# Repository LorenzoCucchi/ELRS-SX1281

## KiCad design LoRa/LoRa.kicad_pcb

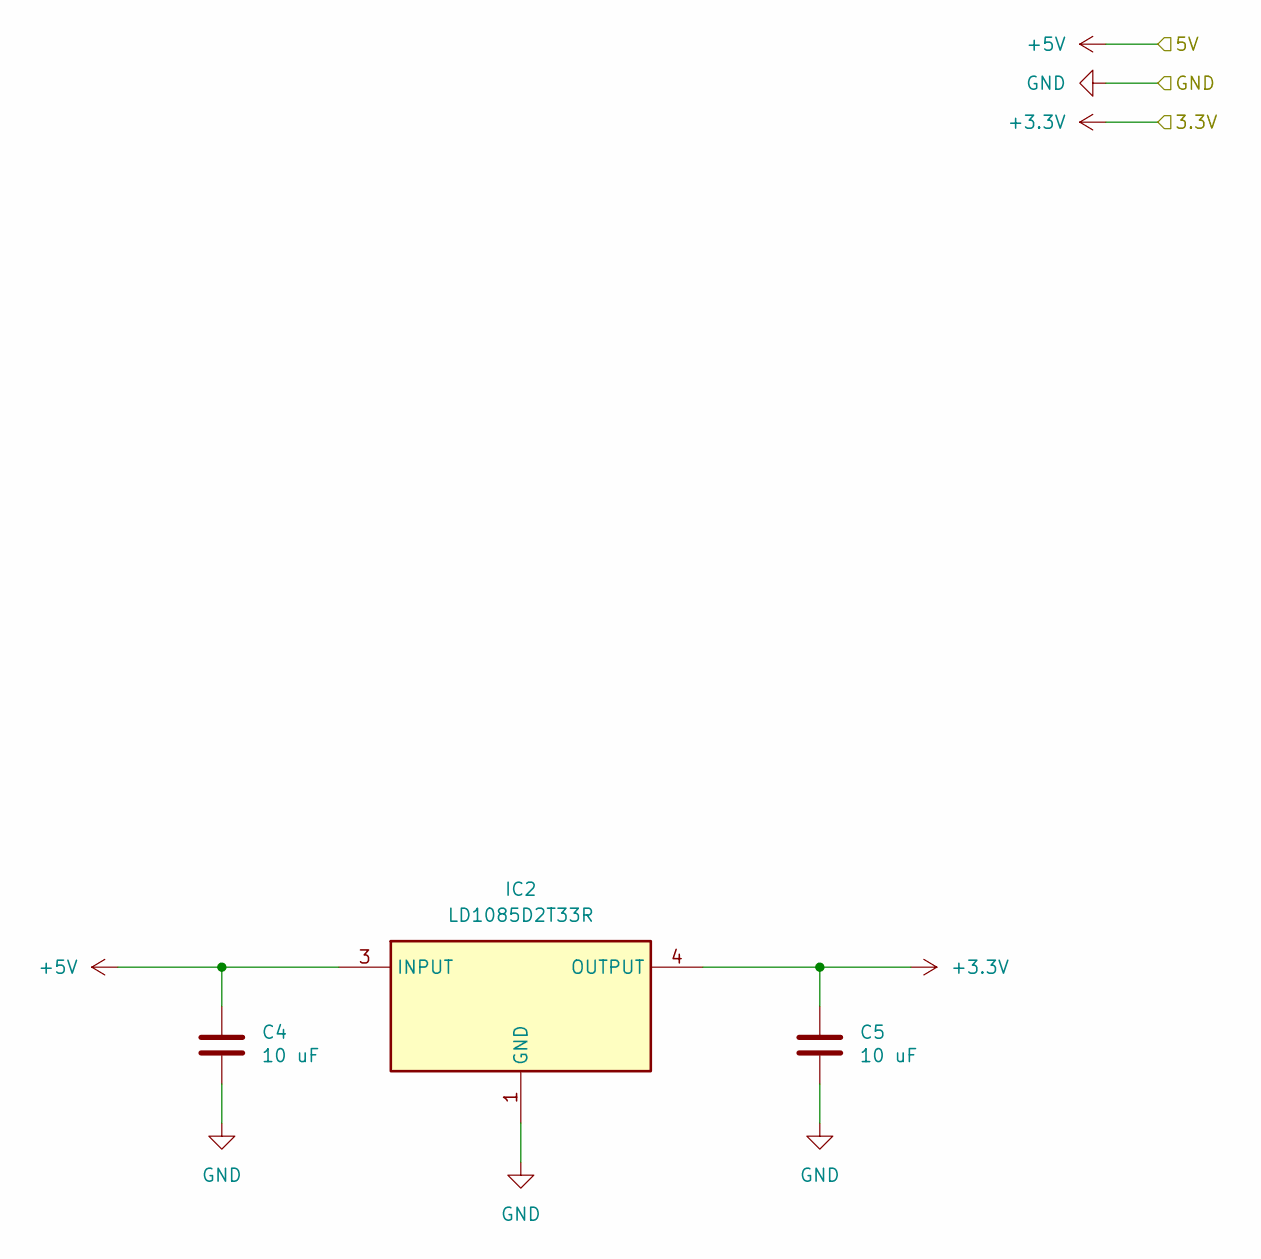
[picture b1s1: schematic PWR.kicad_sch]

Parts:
C4, C5: 10 uF; C_0603_1608Metric_Pad1.08x0.95mm_HandSolder
IC2: LD1085D2T33R; Mouser Part Number 511-LD1085D2T33-TR

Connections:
+3.3V: C5.1, IC2.4 (OUTPUT); also elsewhere on the board
+5V: C4.1, IC2.3 (INPUT); also elsewhere on the board
GND: C4.2, C5.2, IC2.1 (GND); also elsewhere on the board

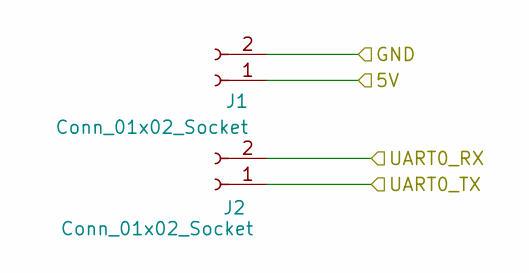
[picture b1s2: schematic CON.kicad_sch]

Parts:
J1, J2: Conn_01x02_Socket; PinHeader_1x02_P2.54mm_Vertical

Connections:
+5V: J1.1; also elsewhere on the board
GND: J1.2; also elsewhere on the board
UART0_RX: J2.2; also elsewhere on the board
UART0_TX: J2.1; also elsewhere on the board

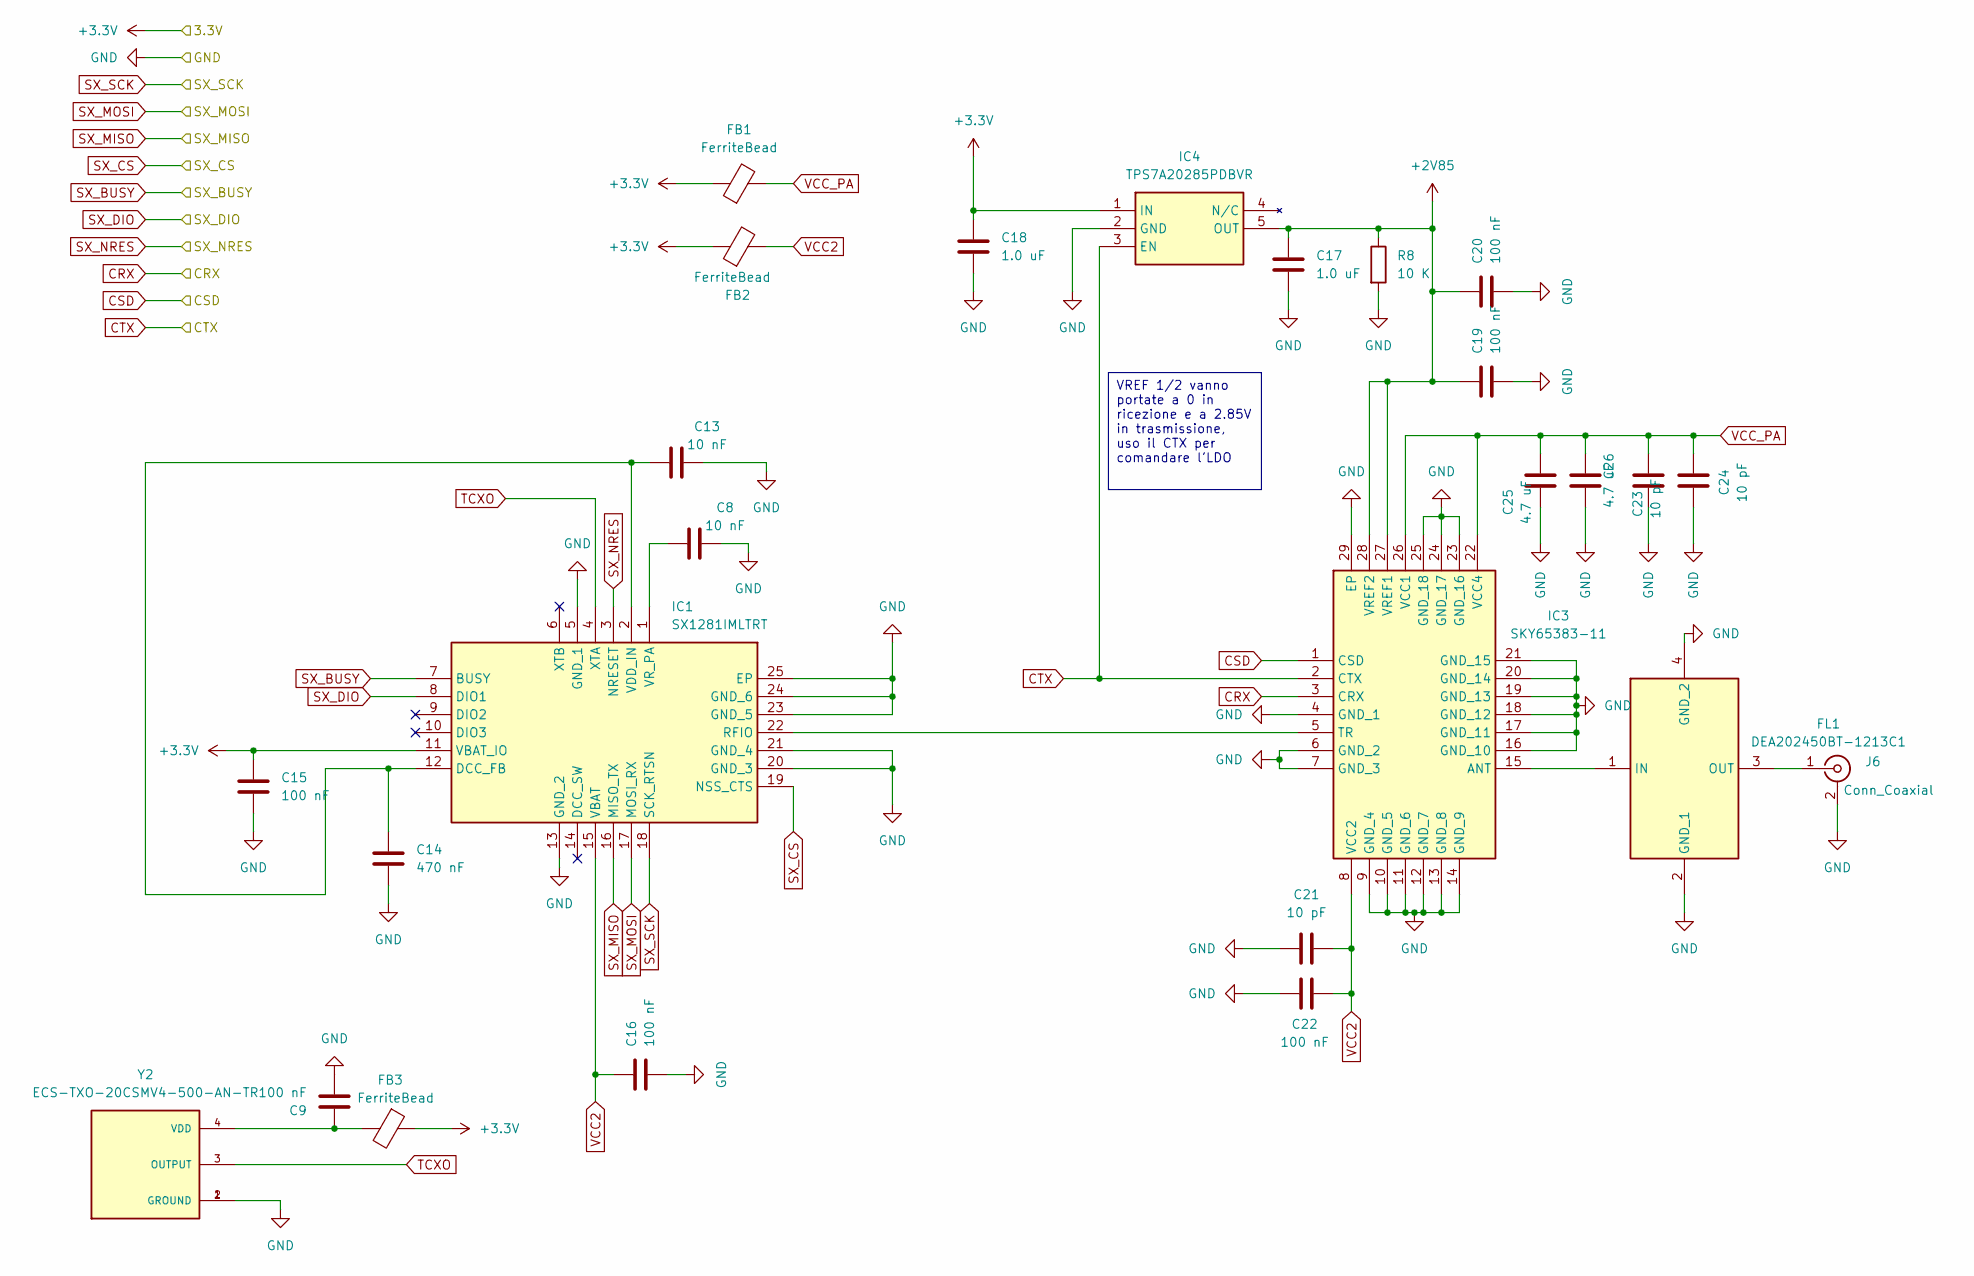
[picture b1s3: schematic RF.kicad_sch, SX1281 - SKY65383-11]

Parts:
C8, C13: 10 nF; C_0603_1608Metric_Pad1.08x0.95mm_HandSolder
C9, C15, C16, C19, C20, C22: 100 nF; C_0603_1608Metric_Pad1.08x0.95mm_HandSolder
C14: 470 nF; C_0603_1608Metric_Pad1.08x0.95mm_HandSolder
C17, C18: 1.0 uF; C_0603_1608Metric_Pad1.08x0.95mm_HandSolder
C21, C23, C24: 10 pF; C_0603_1608Metric_Pad1.08x0.95mm_HandSolder
C25, C26: 4.7 uF; C_0603_1608Metric_Pad1.08x0.95mm_HandSolder
FB1, FB2, FB3: FerriteBead; R_0603_1608Metric_Pad0.98x0.95mm_HandSolder
FL1: DEA202450BT-1213C1; DEA202450BT1213C1; Mouser Part Number 810-DEA22450BT1213C1
IC1: SX1281IMLTRT; QFN50P400X400X100-25N-D; Mouser Part Number 947-SX1281IMLTRT
IC3: SKY65383-11; SKY6538311; Mouser Part Number 873-SKY65383-11
IC4: TPS7A20285PDBVR; SOT95P280X145-5N; Mouser Part Number 595-TPS7A20285PDBVR
J6: Conn_Coaxial; SMA_Samtec_SMA-J-P-H-ST-EM1_EdgeMount
R8: 10 K; R_0603_1608Metric_Pad0.98x0.95mm_HandSolder
Y2: ECS-TXO-20CSMV4-500-AN-TR; OSC_ECS-TXO-20CSMV4-520-AN-TR; PARTREV N/A

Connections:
+2V85: C17.1, C19.1, C20.1, IC3.27 (VREF1), IC3.28 (VREF2), IC4.5 (OUT), R8.1
+3.3V: C15.1, C18.1, FB1.1, FB2.1, FB3.1, IC1.11 (VBAT_IO), IC4.1 (IN); also elsewhere on the board
CRX: IC3.3 (CRX); also elsewhere on the board
CSD: IC3.1 (CSD); also elsewhere on the board
CTX: IC3.2 (CTX), IC4.3 (EN); also elsewhere on the board
GND: C8.2, C9.2, C13.2, C14.2, C15.2, C16.2, C17.2, C18.2, C19.2, C20.2, C21.2, C22.2, C23.2, C24.2, C25.2, C26.2, FL1.2 (GND_1), FL1.4 (GND_2), IC1.5 (GND_1), IC1.13 (GND_2), IC1.20 (GND_3), IC1.21 (GND_4), IC1.23 (GND_5), IC1.24 (GND_6), IC1.25 (EP), IC3.4 (GND_1), IC3.6 (GND_2), IC3.7 (GND_3), IC3.9 (GND_4), IC3.10 (GND_5), IC3.11 (GND_6), IC3.12 (GND_7), IC3.13 (GND_8), IC3.14 (GND_9), IC3.16 (GND_10), IC3.17 (GND_11), IC3.18 (GND_12), IC3.19 (GND_13), IC3.20 (GND_14), IC3.21 (GND_15), IC3.23 (GND_16), IC3.24 (GND_17), IC3.25 (GND_18), IC3.29 (EP), IC4.2 (GND), J6.2 (Ext), R8.2, Y2.1 (GROUND), Y2.2 (GROUND); also elsewhere on the board
unnamed: FL1.1 (IN), IC3.15 (ANT)
unnamed: FL1.3 (OUT), J6.1 (In)
unnamed: C13.1, C14.1, IC1.2 (VDD_IN), IC1.12 (DCC_FB)
unnamed: IC1.22 (RFIO), IC3.5 (TR)
unnamed: C8.1, IC1.1 (VR_PA)
unnamed: C9.1, FB3.2, Y2.4 (VDD)
SX_BUSY: IC1.7 (BUSY); also elsewhere on the board
SX_CS: IC1.19 (NSS_CTS); also elsewhere on the board
SX_DIO: IC1.8 (DIO1); also elsewhere on the board
SX_MISO: IC1.16 (MISO_TX); also elsewhere on the board
SX_MOSI: IC1.17 (MOSI_RX); also elsewhere on the board
SX_NRES: IC1.3 (NRESET); also elsewhere on the board
SX_SCK: IC1.18 (SCK_RTSN); also elsewhere on the board
TCXO: IC1.4 (XTA), Y2.3 (OUTPUT)
VCC2: C16.1, C21.1, C22.1, FB2.2, IC1.15 (VBAT), IC3.8 (VCC2)
VCC_PA: C23.1, C24.1, C25.1, C26.1, FB1.2, IC3.22 (VCC4), IC3.26 (VCC1)

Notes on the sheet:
VREF 1/2 vanno portate a 0 in ricezione e a 2.85V in trasmissione, uso il CTX per comandare l'LDO

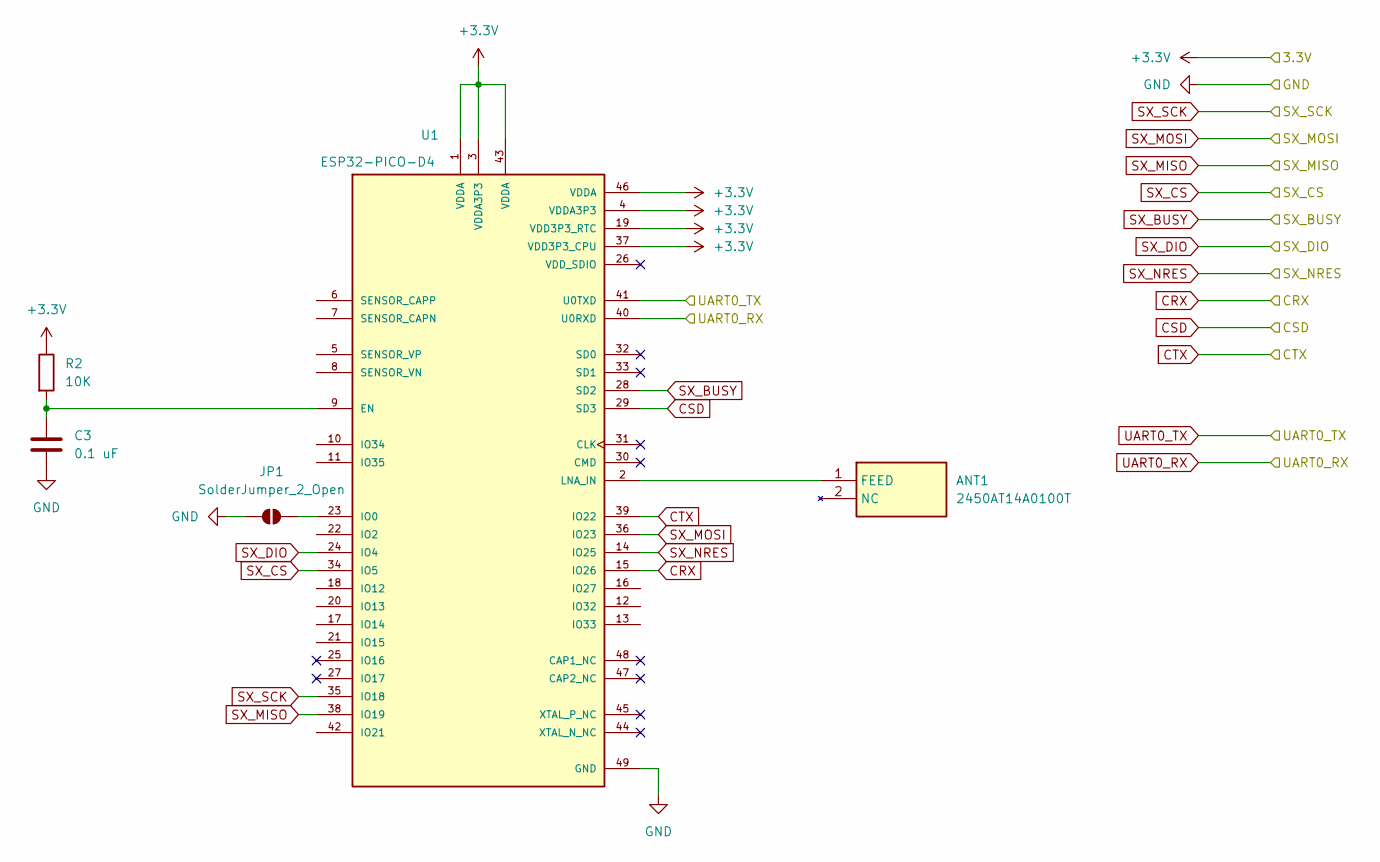
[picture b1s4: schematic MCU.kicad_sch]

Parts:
ANT1: 2450AT14A0100T; ANTC1608X40N; Mouser Part Number 609-2450AT14A0100T
C3: 0.1 uF; C_0603_1608Metric_Pad1.08x0.95mm_HandSolder
JP1: SolderJumper_2_Open; SolderJumper-2_P1.3mm_Open_TrianglePad1.0x1.5mm
R2: 10K; R_0603_1608Metric_Pad0.98x0.95mm_HandSolder
U1: ESP32-PICO-D4; PQFN50P700X700X104-49N; PARTREV v1.9

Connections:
+3.3V: R2.1, U1.1 (VDDA), U1.3 (VDDA3P3), U1.4 (VDDA3P3), U1.19 (VDD3P3_RTC), U1.37 (VDD3P3_CPU), U1.43 (VDDA), U1.46 (VDDA); also elsewhere on the board
CRX: U1.15 (IO26); also elsewhere on the board
CSD: U1.29 (SD3); also elsewhere on the board
CTX: U1.39 (IO22); also elsewhere on the board
GND: C3.2, JP1.1 (A), U1.49 (GND); also elsewhere on the board
unnamed: ANT1.1 (FEED), U1.2 (LNA_IN)
unnamed: JP1.2 (B), U1.23 (IO0)
unnamed: C3.1, R2.2, U1.9 (EN)
SX_BUSY: U1.28 (SD2); also elsewhere on the board
SX_CS: U1.34 (IO5); also elsewhere on the board
SX_DIO: U1.24 (IO4); also elsewhere on the board
SX_MISO: U1.38 (IO19); also elsewhere on the board
SX_MOSI: U1.36 (IO23); also elsewhere on the board
SX_NRES: U1.14 (IO25); also elsewhere on the board
SX_SCK: U1.35 (IO18); also elsewhere on the board
UART0_RX: U1.40 (U0RXD); also elsewhere on the board
UART0_TX: U1.41 (U0TXD); also elsewhere on the board

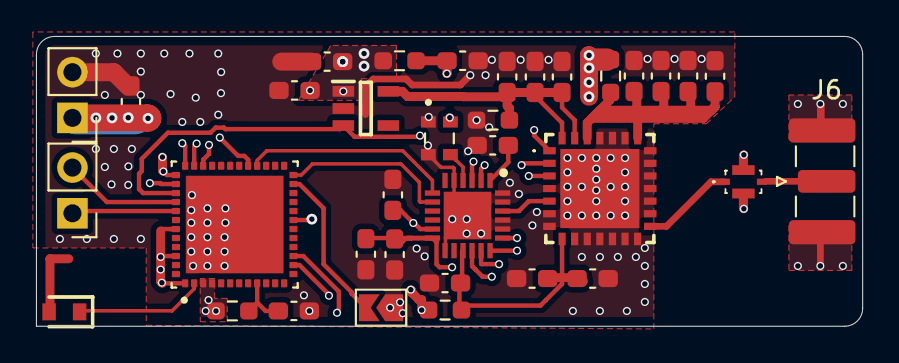
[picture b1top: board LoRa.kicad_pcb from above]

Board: 4 copper layers, 45.9 x 16.1 mm, 36 parts (1 on the bottom side), 28 nets.
